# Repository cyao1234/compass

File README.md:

# Compass

Modular PCB compass powered by ch32v003 and neopixels! Including a built-in magnetic field sensor. You can make a custom Minecraft compass with this!

It is recommended to use [ch32fun](https://github.com/cnlohr/ch32fun?tab=readme-ov-file) with [rv003usb](https://github.com/cnlohr/rv003usb/tree/master/bootloader)

To program the usb bootloader (one time), you can use a pico, arduino, esp32-s2 or whatever!

Features:
- ch32v003
- bunch of neopixels
- art
- easy to use
- board edge usb connector
- usb connection
- ch32
- riscv

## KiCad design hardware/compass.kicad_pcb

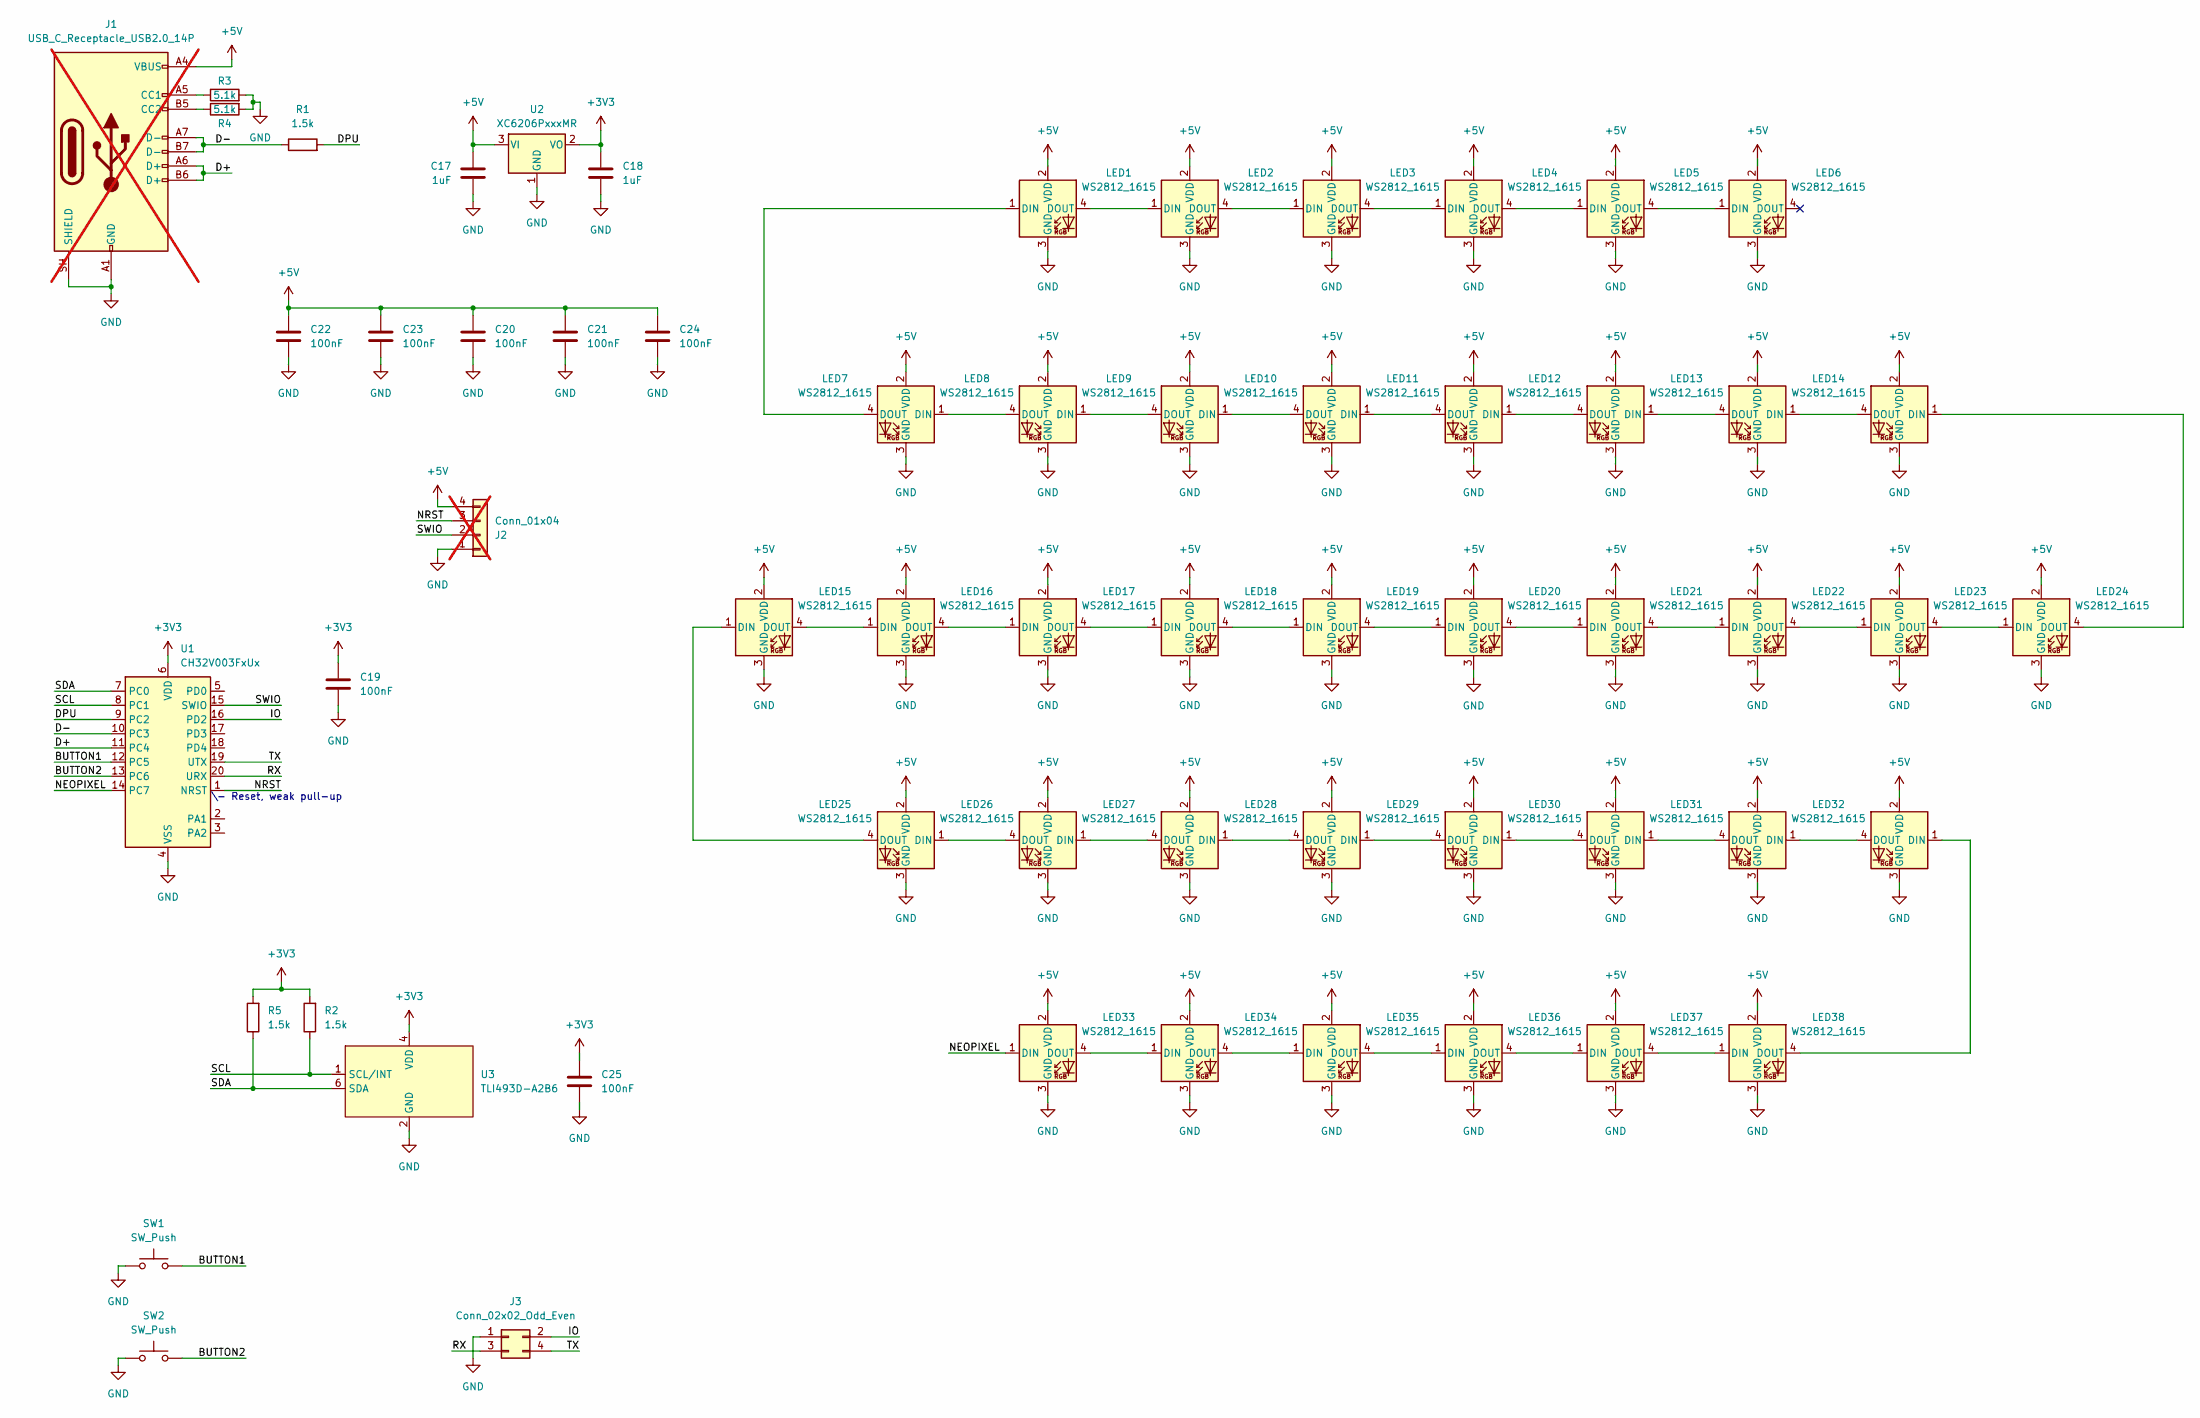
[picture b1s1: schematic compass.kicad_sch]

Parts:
C17, C18: 1uF; C_0402_1005Metric; LCSC Part # C7472946
C19, C20, C21, C22, C23, C24, C25: 100nF; C_0402_1005Metric; LCSC Part # C85858
J1: USB_C_Receptacle_USB2.0_14P; USB_C_PADDLE; not fitted
J2: Conn_01x04; PinHeader_1x04_P2.54mm_Vertical; not fitted
J3: Conn_02x02_Odd_Even; PinSocket_2x02_P2.54mm_Vertical
LED1, LED2, LED3, LED4, LED5, LED6, LED7, LED8, LED9, LED10, LED11, LED12, LED13, LED14, LED15, LED16, LED17, LED18, LED19, LED20, LED21, LED22, LED23, LED24, LED25, LED26, LED27, LED28, LED29, LED30, LED31, LED32, LED33, LED34, LED35, LED36, LED37, LED38: WS2812_1615; LED_WS2812_1615; LCSC Part # C41347987
R1, R2, R5: 1.5k; R_0402_1005Metric; LCSC Part # C2933074
R3, R4: 5.1k; R_0402_1005Metric; LCSC Part # C2906874
SW1, SW2: SW_Push; SW_Push_SPST_TSA016; LCSC Part # C2888428
U1: CH32V003FxUx; QFN-20-1EP_3x3mm_P0.4mm_EP1.65x1.65mm; LCSC Part # C5299908
U2: XC6206PxxxMR; SOT-23-3; LCSC Part # C5252899
U3: TLI493D-A2B6; PG-TSOP6-6-8_1.65x3.05mm_P0.95mm; LCSC Part # C1559664

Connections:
+3V3: C18.1, C19.1, C25.1, R2.2, R5.2, U1.6 (VDD), U2.2 (VO), U3.4 (VDD)
+5V: C17.1, C20.1, C21.1, C22.1, C23.1, C24.1, J1.A4 (VBUS), J1.A9 (VBUS), J1.B4 (VBUS), J1.B9 (VBUS), J2.4, LED1.2 (VDD), LED2.2 (VDD), LED3.2 (VDD), LED4.2 (VDD), LED5.2 (VDD), LED6.2 (VDD), LED7.2 (VDD), LED8.2 (VDD), LED9.2 (VDD), LED10.2 (VDD), LED11.2 (VDD), LED12.2 (VDD), LED13.2 (VDD), LED14.2 (VDD), LED15.2 (VDD), LED16.2 (VDD), LED17.2 (VDD), LED18.2 (VDD), LED19.2 (VDD), LED20.2 (VDD), LED21.2 (VDD), LED22.2 (VDD), LED23.2 (VDD), LED24.2 (VDD), LED25.2 (VDD), LED26.2 (VDD), LED27.2 (VDD), LED28.2 (VDD), LED29.2 (VDD), LED30.2 (VDD), LED31.2 (VDD), LED32.2 (VDD), LED33.2 (VDD), LED34.2 (VDD), LED35.2 (VDD), LED36.2 (VDD), LED37.2 (VDD), LED38.2 (VDD), U2.3 (VI)
/BUTTON1: SW1.2, U1.12 (PC5)
/BUTTON2: SW2.2, U1.13 (PC6)
/D+: J1.A6 (D+), J1.B6 (D+), U1.11 (PC4)
/D-: J1.A7 (D-), J1.B7 (D-), R1.1, U1.10 (PC3)
/DPU: R1.2, U1.9 (PC2)
/IO: J3.2, U1.16 (PD2)
/NEOPIXEL: LED33.1 (DIN), U1.14 (PC7)
/NRST: J2.3, U1.1 (NRST)
/RX: J3.3, U1.20 (URX)
/SCL: R2.1, U1.8 (PC1), U3.1 (SCL/INT)
/SDA: R5.1, U1.7 (PC0), U3.6 (SDA)
/SWIO: J2.2, U1.15 (SWIO)
/TX: J3.4, U1.19 (UTX)
GND: C17.2, C18.2, C19.2, C20.2, C21.2, C22.2, C23.2, C24.2, C25.2, J1.A1 (GND), J1.A12 (GND), J1.B1 (GND), J1.B12 (GND), J1.SH (SHIELD), J2.1, J3.1, LED1.3 (GND), LED2.3 (GND), LED3.3 (GND), LED4.3 (GND), LED5.3 (GND), LED6.3 (GND), LED7.3 (GND), LED8.3 (GND), LED9.3 (GND), LED10.3 (GND), LED11.3 (GND), LED12.3 (GND), LED13.3 (GND), LED14.3 (GND), LED15.3 (GND), LED16.3 (GND), LED17.3 (GND), LED18.3 (GND), LED19.3 (GND), LED21.3 (GND), LED22.3 (GND), LED23.3 (GND), LED24.3 (GND), LED25.3 (GND), LED26.3 (GND), LED27.3 (GND), LED28.3 (GND), LED29.3 (GND), LED30.3 (GND), LED31.3 (GND), LED32.3 (GND), LED33.3 (GND), LED34.3 (GND), LED35.3 (GND), LED36.3 (GND), LED37.3 (GND), LED38.3 (GND), R3.2, R4.2, SW1.1, SW2.1, U1.4 (VSS), U1.21 (VSS), U2.1 (GND), U3.2 (GND), U3.3 (GND), U3.5 (GND)
unnamed: J1.A5 (CC1), R3.1
unnamed: J1.B5 (CC2), R4.1
unnamed: LED1.1 (DIN), LED7.4 (DOUT)
unnamed: LED1.4 (DOUT), LED2.1 (DIN)
unnamed: LED2.4 (DOUT), LED3.1 (DIN)
unnamed: LED3.4 (DOUT), LED4.1 (DIN)
unnamed: LED4.4 (DOUT), LED5.1 (DIN)
unnamed: LED5.4 (DOUT), LED6.1 (DIN)
unnamed: LED7.1 (DIN), LED8.4 (DOUT)
unnamed: LED8.1 (DIN), LED9.4 (DOUT)
unnamed: LED10.1 (DIN), LED11.4 (DOUT)
unnamed: LED9.1 (DIN), LED10.4 (DOUT)
unnamed: LED11.1 (DIN), LED12.4 (DOUT)
unnamed: LED12.1 (DIN), LED13.4 (DOUT)
unnamed: LED13.1 (DIN), LED14.4 (DOUT)
unnamed: LED14.1 (DIN), LED24.4 (DOUT)
unnamed: LED15.1 (DIN), LED25.4 (DOUT)
unnamed: LED15.4 (DOUT), LED16.1 (DIN)
unnamed: LED16.4 (DOUT), LED17.1 (DIN)
unnamed: LED17.4 (DOUT), LED18.1 (DIN)
unnamed: LED18.4 (DOUT), LED19.1 (DIN)
unnamed: LED19.4 (DOUT), LED20.1 (DIN)
unnamed: LED20.4 (DOUT), LED21.1 (DIN)
unnamed: LED21.4 (DOUT), LED22.1 (DIN)
unnamed: LED22.4 (DOUT), LED23.1 (DIN)
unnamed: LED23.4 (DOUT), LED24.1 (DIN)
unnamed: LED25.1 (DIN), LED26.4 (DOUT)
unnamed: LED26.1 (DIN), LED27.4 (DOUT)
unnamed: LED27.1 (DIN), LED28.4 (DOUT)
unnamed: LED28.1 (DIN), LED29.4 (DOUT)
unnamed: LED29.1 (DIN), LED30.4 (DOUT)
unnamed: LED30.1 (DIN), LED31.4 (DOUT)
unnamed: LED31.1 (DIN), LED32.4 (DOUT)
unnamed: LED32.1 (DIN), LED38.4 (DOUT)
unnamed: LED33.4 (DOUT), LED34.1 (DIN)
unnamed: LED34.4 (DOUT), LED35.1 (DIN)
unnamed: LED35.4 (DOUT), LED36.1 (DIN)
unnamed: LED36.4 (DOUT), LED37.1 (DIN)
unnamed: LED37.4 (DOUT), LED38.1 (DIN)

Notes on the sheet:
\- Reset, weak pull-up

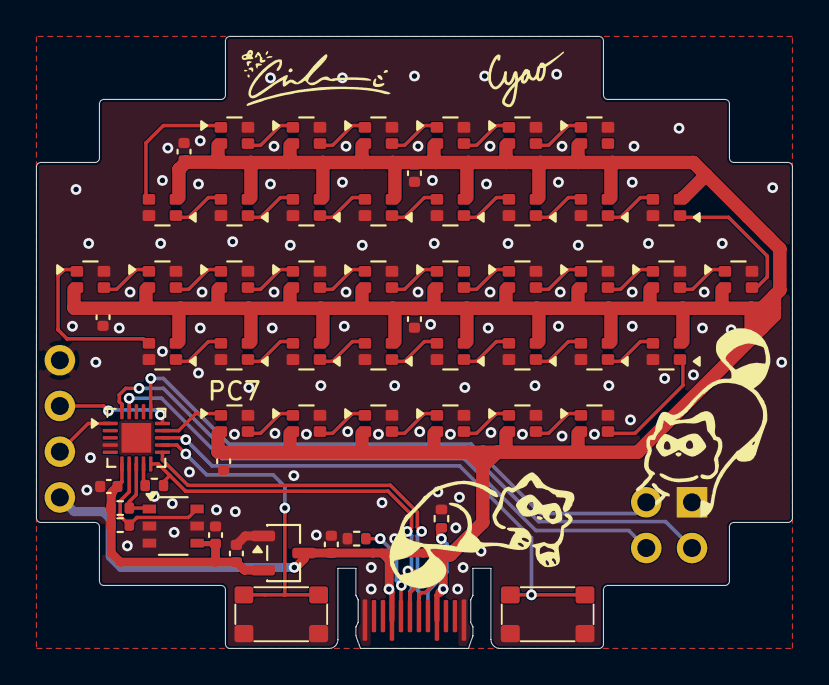
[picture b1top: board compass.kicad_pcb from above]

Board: 2 copper layers, 42.0 x 34.0 mm, 60 parts (0 on the bottom side), 55 nets.

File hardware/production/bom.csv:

Designator,Footprint,Quantity,Value,LCSC Part #
"C17, C18",0402,2,1uF,C7472946
"C19, C20, C21, C22, C23, C24, C25",0402,7,100nF,C85858
J3,PinSocket_2x02_P2.54mm_Vertical,1,Conn_02x02_Odd_Even,
"LED1, LED10, LED11, LED12, LED13, LED14, LED15, LED16, LED17, LED18, LED19, LED2, LED20, LED21, LED22, LED23, LED24, LED25, LED26, LED27, LED28, LED29, LED3, LED30, LED31, LED32, LED33, LED34, LED35, LED36, LED37, LED38, LED4, LED5, LED6, LED7, LED8, LED9",LED_WS2812_1615,38,WS2812_1615,C41347987
"R1, R2, R5",0402,3,1.5k,C2933074
"R3, R4",0402,2,5.1k,C2906874
"SW1, SW2",SW_Push_SPST_TSA016,2,SW_Push,C2888428
U1,QFN-20-1EP_3x3mm_P0.4mm_EP1.65x1.65mm,1,CH32V003FxUx,C5299908
U2,SOT-23-3,1,XC6206PxxxMR,C5252899
U3,PG-TSOP6-6-8_1.65x3.05mm_P0.95mm,1,TLI493D-A2B6,C1559664
